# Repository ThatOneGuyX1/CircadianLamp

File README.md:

# Circadian Lamp

## Overview
The Circadian Lamp project aims to create a smart lighting system that mimics natural light patterns and help user wake up the time they want.
## Breakdown of Different Systems
### 1. Lighting Control System
The lighting control system manages the intensity and color temperature of the LEDs to simulate natural daylight.

### 2. Sensor System
The sensor system includes light sensors and possibly other environmental sensors to adjust the lighting based on ambient conditions.

### 3. Power Management System
The power management system ensures efficient power delivery to the LEDs and other components.

### 4. User Interface
The user interface allows users to control the lamp settings manually or set schedules.

## Hardware BOM
| Component Name | Component Item on PCB | Price | Link |
|----------------|------------------------|-------|------|
| LED Driver     | U1                     | $5.00 | [Link](http://example.com) |
| Light Sensor   | U2                     | $2.50 | [Link](http://example.com) |
| Microcontroller| U3                     | $10.00| [Link](http://example.com) |
| Power Supply   | U4                     | $8.00 | [Link](http://example.com) |
| PCB            | -                      | $15.00| [Link](http://example.com) |

## Major Revisions
### V 1.0.0
The orginal this includes using a RasPi Pico to handle the logic, a basic PWM amplifer and high side switch using MOSFET transitors. It is not powered by USB-C PD but by an external source.

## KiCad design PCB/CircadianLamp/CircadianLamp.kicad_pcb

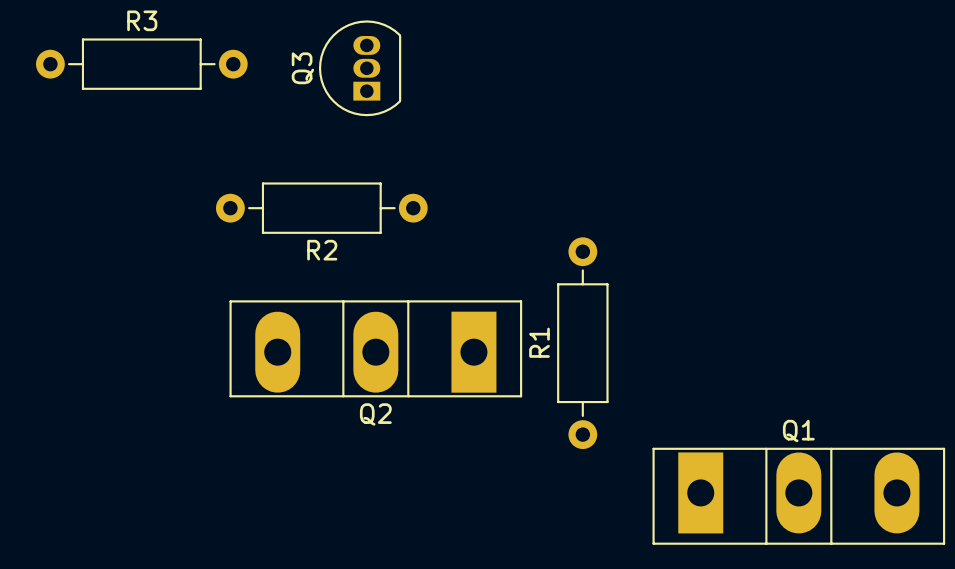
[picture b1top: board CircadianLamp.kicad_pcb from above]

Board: 2 copper layers, 6 parts (0 on the bottom side), 5 nets, no tracks yet.

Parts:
Q1: NMOS; TO-247-3_Vertical
Q2: PMOS; TO-247-3_Vertical
Q3: 2N3904; TO-92_Inline
R1, R2, R3: R; R_Axial_DIN0207_L6.3mm_D2.5mm_P10.16mm_Horizontal

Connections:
unnamed: Q2.1 (D), R1.2
unnamed: Q2.2 (G), Q3.3 (C), R2.1
unnamed: Q3.2 (B), R3.2
V-Source: Q2.3 (S), R2.2
V_out: Q1.1 (D), R1.1

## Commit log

2025-02-20 Added README and PCB
